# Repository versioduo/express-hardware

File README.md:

# express-hardware

🎚️ 16 Channel Expression Controller

## Board

## Schematic

[PDF](express.pdf)

## Bill Of Materials

[Interactive BOM](https://htmlpreview.github.io/?https://github.com/versioduo/express-hardware/main/express-bom.html)

# Copying
Anyone can use this public domain work without having to seek authorisation, no one can ever own it.

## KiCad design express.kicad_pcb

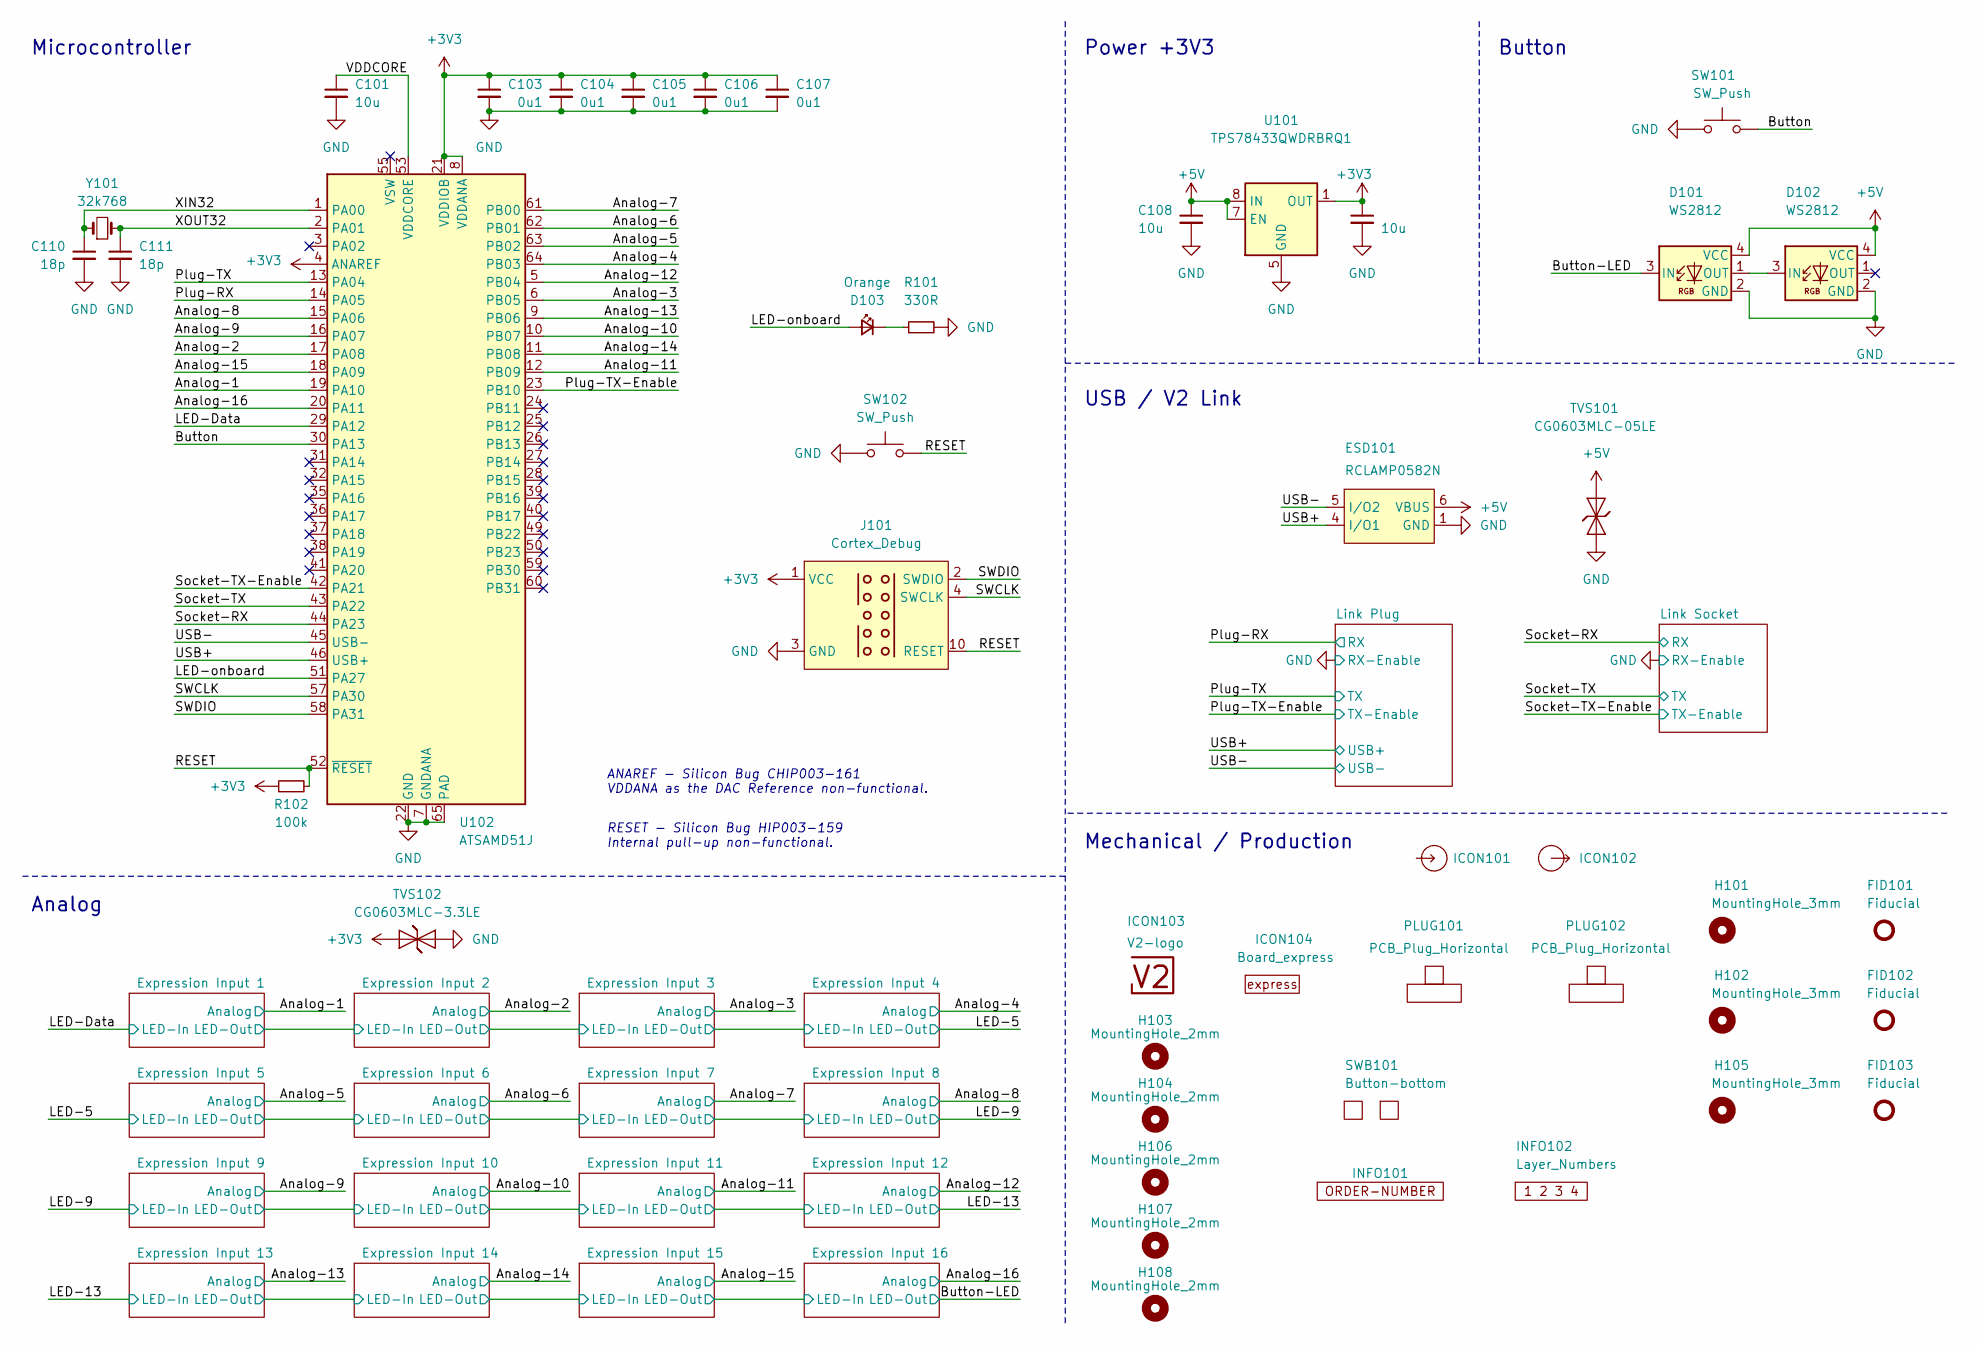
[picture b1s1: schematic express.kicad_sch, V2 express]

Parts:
C101, C108, C109: 10u; C_0603_1608Metric
C103, C104, C105, C106, C107: 0u1; C_0603_1608Metric
C110, C111: 18p; C_0603_1608Metric
D101, D102: WS2812; WS2812-2020
D103: Orange; LED_0603_1608Metric
ESD101: RCLAMP0582N; SLP1210N6
FID101, FID102, FID103: Fiducial; Fiducial_0.5mm_Mask1mm_Paste
H101, H102, H105: MountingHole_3mm
H103, H104, H106, H107, H108: MountingHole_2mm
ICON101: Arrow_In
ICON102: Arrow_Out
ICON103: V2-logo; Logo_Small
ICON104: Board_express; Board_express_Small
INFO101: Order_Number
INFO102: Layer_Numbers
J101: Cortex_Debug; Cortex_Debug_Pad
PLUG101, PLUG102: PCB_Plug_Horizontal
R101: 330R; R_0603_1608Metric
R102: 100k; R_0603_1608Metric
SW101, SW102: SW_Push; SKSG
SWB101: Button-bottom; PCB_Button-bottom
TVS101: CG0603MLC-05LE; D_0603_1608Metric
TVS102: CG0603MLC-3.3LE; D_0603_1608Metric
U101: TPS78433QWDRBRQ1; VSON-8-1_3x3mm_P0.65_EP1.65x2.4mm
U102: ATSAMD51J; QFN-64-1EP_9x9mm_P0.5mm_EP4.8x4.8mm_ThermalVias
Y101: 32k768; Crystal_SMD_3215-2Pin_3.2x1.5mm

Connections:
+3V3: C103.1, C104.1, C105.1, C106.1, C107.1, C109.1, J101.1 (VCC), R102.1, TVS102.1 (K), U101.1 (OUT), U102.4 (ANAREF), U102.8 (VDDANA), U102.21 (VDDIOB), U102.34 (VDDIO), U102.48 (VDDIO), U102.56 (VDDIO); also elsewhere on the board
+5V: C108.1, D101.4 (VCC), D102.4 (VCC), ESD101.6 (VBUS), TVS101.2 (A), U101.7 (EN), U101.8 (IN); also elsewhere on the board
/Analog-1: U102.19 (PA10); also elsewhere on the board
/Analog-2: U102.17 (PA08); also elsewhere on the board
/Analog-3: U102.6 (PB05); also elsewhere on the board
/Analog-4: U102.64 (PB03); also elsewhere on the board
/Analog-5: U102.63 (PB02); also elsewhere on the board
/Analog-6: U102.62 (PB01); also elsewhere on the board
/Analog-7: U102.61 (PB00); also elsewhere on the board
/Analog-8: U102.15 (PA06); also elsewhere on the board
/Analog-9: U102.16 (PA07); also elsewhere on the board
/Analog-10: U102.10 (PB07); also elsewhere on the board
/Analog-11: U102.12 (PB09); also elsewhere on the board
/Analog-12: U102.5 (PB04); also elsewhere on the board
/Analog-13: U102.9 (PB06); also elsewhere on the board
/Analog-14: U102.11 (PB08); also elsewhere on the board
/Analog-15: U102.18 (PA09); also elsewhere on the board
/Analog-16: U102.20 (PA11); also elsewhere on the board
/Button: SW101.2, U102.30 (PA13)
/Button-LED: D101.3 (IN); also elsewhere on the board
/LED-Data: U102.29 (PA12); also elsewhere on the board
/LED-onboard: D103.2 (A), U102.51 (PA27)
/Plug-RX: U102.14 (PA05); also elsewhere on the board
/Plug-TX: U102.13 (PA04); also elsewhere on the board
/Plug-TX-Enable: U102.23 (PB10); also elsewhere on the board
/RESET: J101.10 (RESET), R102.2, SW102.2, U102.52 (~RESET)
/SWCLK: J101.4 (SWCLK), U102.57 (PA30)
/SWDIO: J101.2 (SWDIO), U102.58 (PA31)
/Socket-RX: U102.44 (PA23); also elsewhere on the board
/Socket-TX: U102.43 (PA22); also elsewhere on the board
/Socket-TX-Enable: U102.42 (PA21); also elsewhere on the board
/USB+: ESD101.4 (I/O1), U102.46 (USB+); also elsewhere on the board
/USB-: ESD101.5 (I/O2), U102.45 (USB-); also elsewhere on the board
/VDDCORE: C101.1, U102.53 (VDDCORE)
/XIN32: C110.1, U102.1 (PA00), Y101.1
/XOUT32: C111.1, U102.2 (PA01), Y101.2
GND: C101.2, C103.2, C104.2, C105.2, C106.2, C107.2, C108.2, C109.2, C110.2, C111.2, D101.2 (GND), D102.2 (GND), ESD101.1 (GND), J101.3 (GND), J101.5 (GND), R101.2, SW101.1, SW102.1, TVS101.1 (K), TVS102.2 (A), U101.5 (GND), U101.9 (GND), U102.7 (GNDANA), U102.22 (GND), U102.33 (GND), U102.47 (GND), U102.54 (GND), U102.65 (PAD); also elsewhere on the board
unnamed: D101.1 (OUT), D102.3 (IN)
unnamed: D103.1 (K), R101.1

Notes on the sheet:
ANAREF - ﻿Silicon Bug CHIP003-161 VDDANA as the DAC Reference non-functional.
Analog
RESET - ﻿Silicon Bug HIP003-159 Internal pull-up non-functional.
Button
Power +3V3
Mechanical / Production
Microcontroller
USB / V2 Link

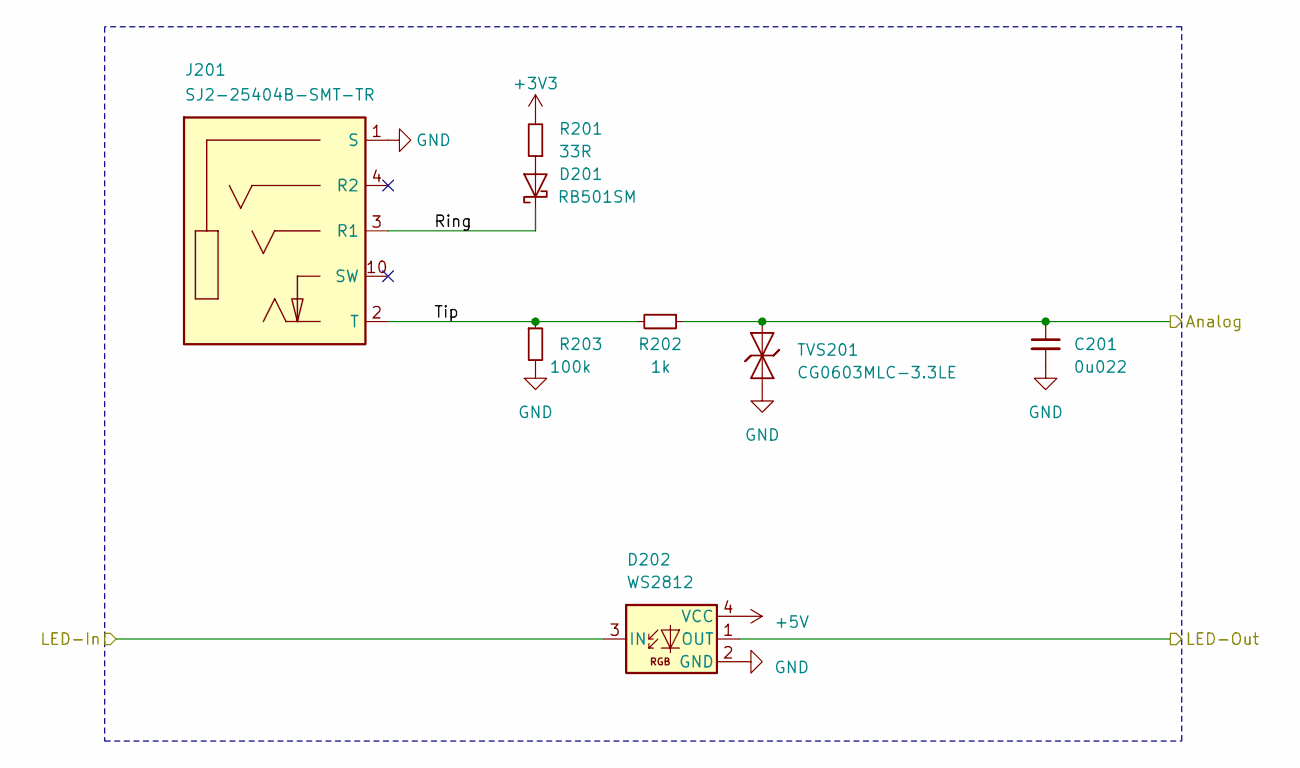
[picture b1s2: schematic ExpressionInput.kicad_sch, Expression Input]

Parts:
C201: 0u022; C_0603_1608Metric
D201: RB501SM; D_SOD-523
D202: WS2812; WS2812-2020
J201: SJ2-25404B-SMT-TR; CUI_SJ2-25404B-SMT-TR
R201: 33R; R_0603_1608Metric
R202: 1k; R_0603_1608Metric
R203: 100k; R_0603_1608Metric
TVS201: CG0603MLC-3.3LE; D_0603_1608Metric

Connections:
+3V3: R201.2; also elsewhere on the board
+5V: D202.4 (VCC); also elsewhere on the board
/ Expression Input 1/LED-Out: D202.1 (OUT); also elsewhere on the board
/ Expression Input 1/Ring: D201.1 (K), J201.3 (R1)
/ Expression Input 1/Tip: J201.2 (T), R202.2, R203.1
/Analog-1: C201.1, R202.1, TVS201.2 (A); also elsewhere on the board
/LED-Data: D202.3 (IN); also elsewhere on the board
GND: C201.2, D202.2 (GND), J201.1 (S), R203.2, TVS201.1 (K); also elsewhere on the board
unnamed: D201.2 (A), R201.1

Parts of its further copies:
C301, C401, C501, C601, C701, C801, C901, C1001, C1101, C1201, C1301, C1401, C1501, C1601, C1701: 0u022; C_0603_1608Metric
D301, D401, D501, D601, D701, D801, D901, D1001, D1101, D1201, D1301, D1401, D1501, D1601, D1701: RB501SM; D_SOD-523
D302, D402, D502, D602, D702, D802, D902, D1002, D1102, D1202, D1302, D1402, D1502, D1602, D1702: WS2812; WS2812-2020
J301, J401, J501, J601, J701, J801, J901, J1001, J1101, J1201, J1301, J1401, J1501, J1601, J1701: SJ2-25404B-SMT-TR; CUI_SJ2-25404B-SMT-TR
R301, R401, R501, R601, R701, R801, R901, R1001, R1101, R1201, R1301, R1401, R1501, R1601, R1701: 33R; R_0603_1608Metric
R302, R402, R502, R602, R702, R802, R902, R1002, R1102, R1202, R1302, R1402, R1502, R1602, R1702: 1k; R_0603_1608Metric
R303, R403, R503, R603, R703, R803, R903, R1003, R1103, R1203, R1303, R1403, R1503, R1603, R1703: 100k; R_0603_1608Metric
TVS301, TVS401, TVS501, TVS601, TVS701, TVS801, TVS901, TVS1001, TVS1101, TVS1201, TVS1301, TVS1401, TVS1501, TVS1601, TVS1701: CG0603MLC-3.3LE; D_0603_1608Metric

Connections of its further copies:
+3V3: R301.2, R401.2, R501.2, R601.2, R701.2, R801.2, R901.2, R1001.2, R1101.2, R1201.2, R1301.2, R1401.2, R1501.2, R1601.2, R1701.2; also elsewhere on the board
+5V: D302.4 (VCC), D402.4 (VCC), D502.4 (VCC), D602.4 (VCC), D702.4 (VCC), D802.4 (VCC), D902.4 (VCC), D1002.4 (VCC), D1102.4 (VCC), D1202.4 (VCC), D1302.4 (VCC), D1402.4 (VCC), D1502.4 (VCC), D1602.4 (VCC), D1702.4 (VCC); also elsewhere on the board
/ Expression Input 1/LED-Out: D302.3 (IN); also elsewhere on the board
/ Expression Input 2/LED-Out: D302.1 (OUT), D402.3 (IN)
/ Expression Input 2/Ring: D301.1 (K), J301.3 (R1)
/ Expression Input 2/Tip: J301.2 (T), R302.2, R303.1
/ Expression Input 3/LED-Out: D402.1 (OUT), D502.3 (IN)
/ Expression Input 3/Ring: D401.1 (K), J401.3 (R1)
/ Expression Input 3/Tip: J401.2 (T), R402.2, R403.1
/ Expression Input 4/Ring: D501.1 (K), J501.3 (R1)
/ Expression Input 4/Tip: J501.2 (T), R502.2, R503.1
/ Expression Input 5 /LED-Out: D602.1 (OUT), D702.3 (IN)
/ Expression Input 5 /Ring: D601.1 (K), J601.3 (R1)
/ Expression Input 5 /Tip: J601.2 (T), R602.2, R603.1
/ Expression Input 6/LED-Out: D702.1 (OUT), D802.3 (IN)
/ Expression Input 6/Ring: D701.1 (K), J701.3 (R1)
/ Expression Input 6/Tip: J701.2 (T), R702.2, R703.1
/ Expression Input 7/LED-Out: D802.1 (OUT), D902.3 (IN)
/ Expression Input 7/Ring: D801.1 (K), J801.3 (R1)
/ Expression Input 7/Tip: J801.2 (T), R802.2, R803.1
/ Expression Input 8/Ring: D901.1 (K), J901.3 (R1)
/ Expression Input 8/Tip: J901.2 (T), R902.2, R903.1
/ Expression Input 9/Ring: D1001.1 (K), J1001.3 (R1)
/ Expression Input 9/Tip: J1001.2 (T), R1002.2, R1003.1
/ Expression Input 10/LED-In: D1002.1 (OUT), D1102.3 (IN)
/ Expression Input 10/LED-Out: D1102.1 (OUT), D1202.3 (IN)
/ Expression Input 10/Ring: D1101.1 (K), J1101.3 (R1)
/ Expression Input 10/Tip: J1101.2 (T), R1102.2, R1103.1
/ Expression Input 11/LED-Out: D1202.1 (OUT), D1302.3 (IN)
/ Expression Input 11/Ring: D1201.1 (K), J1201.3 (R1)
/ Expression Input 11/Tip: J1201.2 (T), R1202.2, R1203.1
/ Expression Input 12/Ring: D1301.1 (K), J1301.3 (R1)
/ Expression Input 12/Tip: J1301.2 (T), R1302.2, R1303.1
/ Expression Input 13/LED-Out: D1402.1 (OUT), D1502.3 (IN)
/ Expression Input 13/Ring: D1401.1 (K), J1401.3 (R1)
/ Expression Input 13/Tip: J1401.2 (T), R1402.2, R1403.1
/ Expression Input 14/LED-Out: D1502.1 (OUT), D1602.3 (IN)
/ Expression Input 14/Ring: D1501.1 (K), J1501.3 (R1)
/ Expression Input 14/Tip: J1501.2 (T), R1502.2, R1503.1
/ Expression Input 15/LED-Out: D1602.1 (OUT), D1702.3 (IN)
/ Expression Input 15/Ring: D1601.1 (K), J1601.3 (R1)
/ Expression Input 15/Tip: J1601.2 (T), R1602.2, R1603.1
/ Expression Input 16/Ring: D1701.1 (K), J1701.3 (R1)
/ Expression Input 16/Tip: J1701.2 (T), R1702.2, R1703.1
/Analog-2: C301.1, R302.1, TVS301.2 (A); also elsewhere on the board
/Analog-3: C401.1, R402.1, TVS401.2 (A); also elsewhere on the board
/Analog-4: C501.1, R502.1, TVS501.2 (A); also elsewhere on the board
/Analog-5: C601.1, R602.1, TVS601.2 (A); also elsewhere on the board
/Analog-6: C701.1, R702.1, TVS701.2 (A); also elsewhere on the board
/Analog-7: C801.1, R802.1, TVS801.2 (A); also elsewhere on the board
/Analog-8: C901.1, R902.1, TVS901.2 (A); also elsewhere on the board
/Analog-9: C1001.1, R1002.1, TVS1001.2 (A); also elsewhere on the board
/Analog-10: C1101.1, R1102.1, TVS1101.2 (A); also elsewhere on the board
/Analog-11: C1201.1, R1202.1, TVS1201.2 (A); also elsewhere on the board
/Analog-12: C1301.1, R1302.1, TVS1301.2 (A); also elsewhere on the board
/Analog-13: C1401.1, R1402.1, TVS1401.2 (A); also elsewhere on the board
/Analog-14: C1501.1, R1502.1, TVS1501.2 (A); also elsewhere on the board
/Analog-15: C1601.1, R1602.1, TVS1601.2 (A); also elsewhere on the board
/Analog-16: C1701.1, R1702.1, TVS1701.2 (A); also elsewhere on the board
/Button-LED: D1702.1 (OUT); also elsewhere on the board
/LED-5: D502.1 (OUT), D602.3 (IN)
/LED-9: D902.1 (OUT), D1002.3 (IN)
/LED-13: D1302.1 (OUT), D1402.3 (IN)
GND: C301.2, C401.2, C501.2, C601.2, C701.2, C801.2, C901.2, C1001.2, C1101.2, C1201.2, C1301.2, C1401.2, C1501.2, C1601.2, C1701.2, D302.2 (GND), D402.2 (GND), D502.2 (GND), D602.2 (GND), D702.2 (GND), D802.2 (GND), D902.2 (GND), D1002.2 (GND), D1102.2 (GND), D1202.2 (GND), D1302.2 (GND), D1402.2 (GND), D1502.2 (GND), D1602.2 (GND), D1702.2 (GND), J301.1 (S), J401.1 (S), J501.1 (S), J601.1 (S), J701.1 (S), J801.1 (S), J901.1 (S), J1001.1 (S), J1101.1 (S), J1201.1 (S), J1301.1 (S), J1401.1 (S), J1501.1 (S), J1601.1 (S), J1701.1 (S), R303.2, R403.2, R503.2, R603.2, R703.2, R803.2, R903.2, R1003.2, R1103.2, R1203.2, R1303.2, R1403.2, R1503.2, R1603.2, R1703.2, TVS301.1 (K), TVS401.1 (K), TVS501.1 (K), TVS601.1 (K), TVS701.1 (K), TVS801.1 (K), TVS901.1 (K), TVS1001.1 (K), TVS1101.1 (K), TVS1201.1 (K), TVS1301.1 (K), TVS1401.1 (K), TVS1501.1 (K), TVS1601.1 (K), TVS1701.1 (K); also elsewhere on the board
unnamed: D301.2 (A), R301.1
unnamed: D401.2 (A), R401.1
unnamed: D501.2 (A), R501.1
unnamed: D601.2 (A), R601.1
unnamed: D701.2 (A), R701.1
unnamed: D801.2 (A), R801.1
unnamed: D901.2 (A), R901.1
unnamed: D1001.2 (A), R1001.1
unnamed: D1101.2 (A), R1101.1
unnamed: D1201.2 (A), R1201.1
unnamed: D1301.2 (A), R1301.1
unnamed: D1401.2 (A), R1401.1
unnamed: D1501.2 (A), R1501.1
unnamed: D1601.2 (A), R1601.1
unnamed: D1701.2 (A), R1701.1

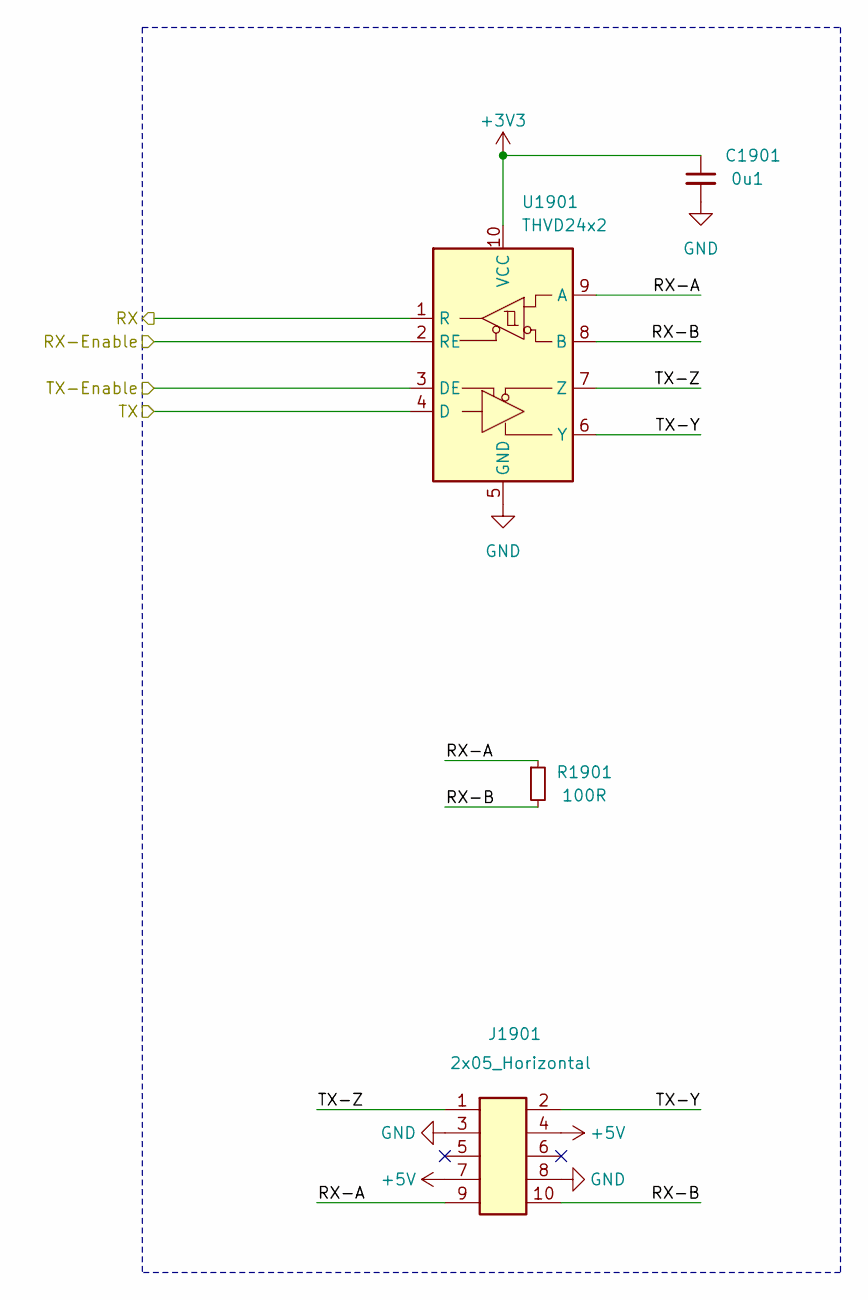
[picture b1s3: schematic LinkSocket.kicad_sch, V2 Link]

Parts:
C1901: 0u1; C_0603_1608Metric
J1901: 2x05_Horizontal; PinHeader_2x05_P1.27mm_Horizontal
R1901: 100R; R_0603_1608Metric
U1901: THVD24x2; VSON-10-4-1EP_3x3mm_P0.5mm_EP1.65x2.4mm_ThermalVias

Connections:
+3V3: C1901.1, U1901.10 (VCC); also elsewhere on the board
+5V: J1901.4, J1901.7; also elsewhere on the board
/Link Socket/RX-A: J1901.9, R1901.1, U1901.9 (A)
/Link Socket/RX-B: J1901.10, R1901.2, U1901.8 (B)
/Link Socket/TX-Y: J1901.2, U1901.6 (Y)
/Link Socket/TX-Z: J1901.1, U1901.7 (Z)
/Socket-RX: U1901.1 (R); also elsewhere on the board
/Socket-TX: U1901.4 (D); also elsewhere on the board
/Socket-TX-Enable: U1901.3 (DE); also elsewhere on the board
GND: C1901.2, J1901.3, J1901.8, U1901.2 (RE), U1901.5 (GND), U1901.11 (GND); also elsewhere on the board

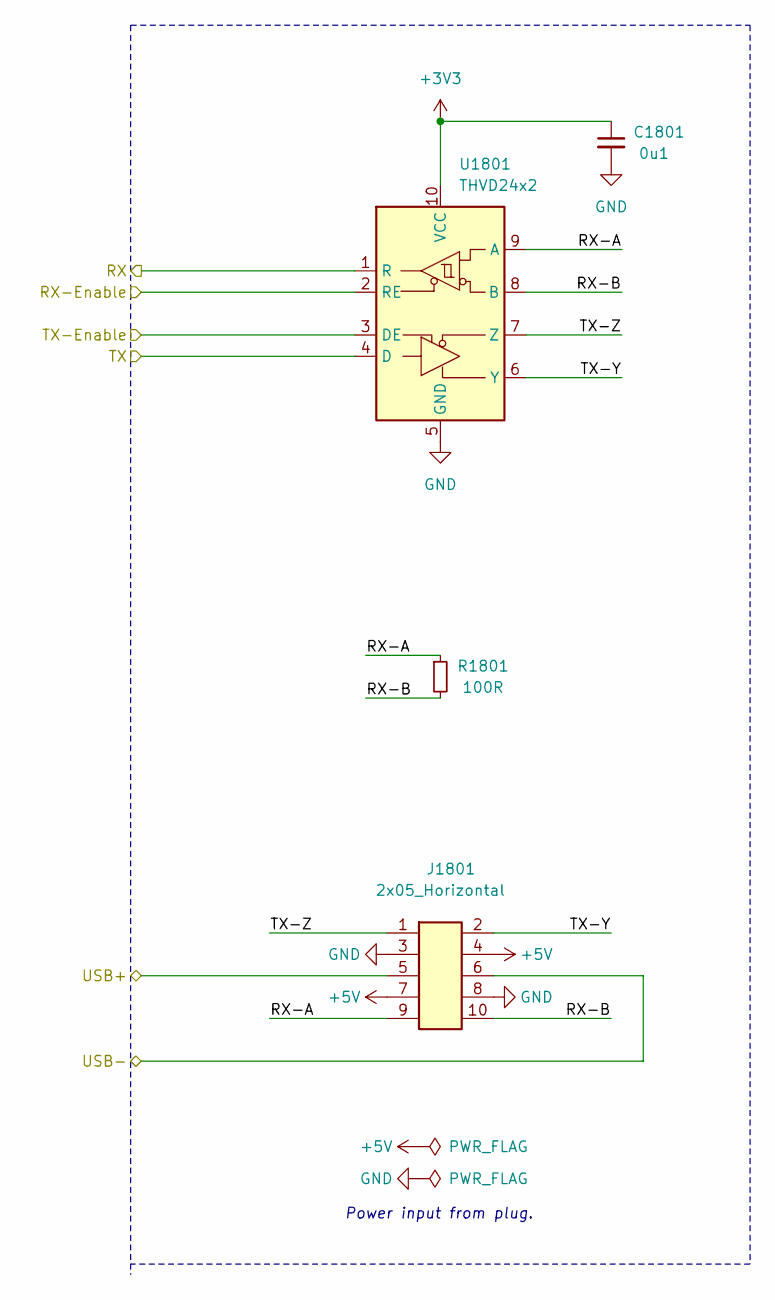
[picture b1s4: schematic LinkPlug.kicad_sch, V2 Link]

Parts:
C1801: 0u1; C_0603_1608Metric
J1801: 2x05_Horizontal; PinHeader_2x05_P1.27mm_Horizontal
R1801: 100R; R_0603_1608Metric
U1801: THVD24x2; VSON-10-4-1EP_3x3mm_P0.5mm_EP1.65x2.4mm_ThermalVias

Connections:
+3V3: C1801.1, U1801.10 (VCC); also elsewhere on the board
+5V: J1801.4, J1801.7; also elsewhere on the board
/Link Plug/RX-A: J1801.9, R1801.1, U1801.9 (A)
/Link Plug/RX-B: J1801.10, R1801.2, U1801.8 (B)
/Link Plug/TX-Y: J1801.2, U1801.6 (Y)
/Link Plug/TX-Z: J1801.1, U1801.7 (Z)
/Plug-RX: U1801.1 (R); also elsewhere on the board
/Plug-TX: U1801.4 (D); also elsewhere on the board
/Plug-TX-Enable: U1801.3 (DE); also elsewhere on the board
/USB+: J1801.5; also elsewhere on the board
/USB-: J1801.6; also elsewhere on the board
GND: C1801.2, J1801.3, J1801.8, U1801.2 (RE), U1801.5 (GND), U1801.11 (GND); also elsewhere on the board

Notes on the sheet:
Power input from plug.

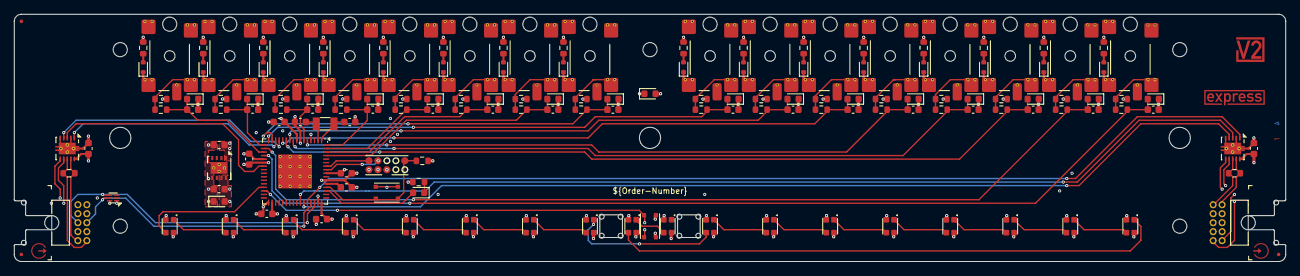
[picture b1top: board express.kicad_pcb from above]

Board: 4 copper layers, 180.0 x 35.0 mm, 180 parts (0 on the bottom side), 110 nets.

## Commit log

2023-03-01 Import
2023-06-04 Replace MIDI In with MIDI Out
2023-07-01 Refresh
2024-01-14 KiCad 8
2024-02-03 Use larger vias
2024-03-11 Use the correct TRS pins
2024-03-12 Udpate
2024-03-28 Update to Kicad 8
2024-07-07 Fix LED location
2024-07-17 Replace TRS sockets
2024-09-26 Update TRS sockets
2025-09-19 Convert to V2 Link
2025-10-01 Move transceiver
2025-10-27 Update tranceiver
2025-11-28 Link termination
2025-11-28 Colours
